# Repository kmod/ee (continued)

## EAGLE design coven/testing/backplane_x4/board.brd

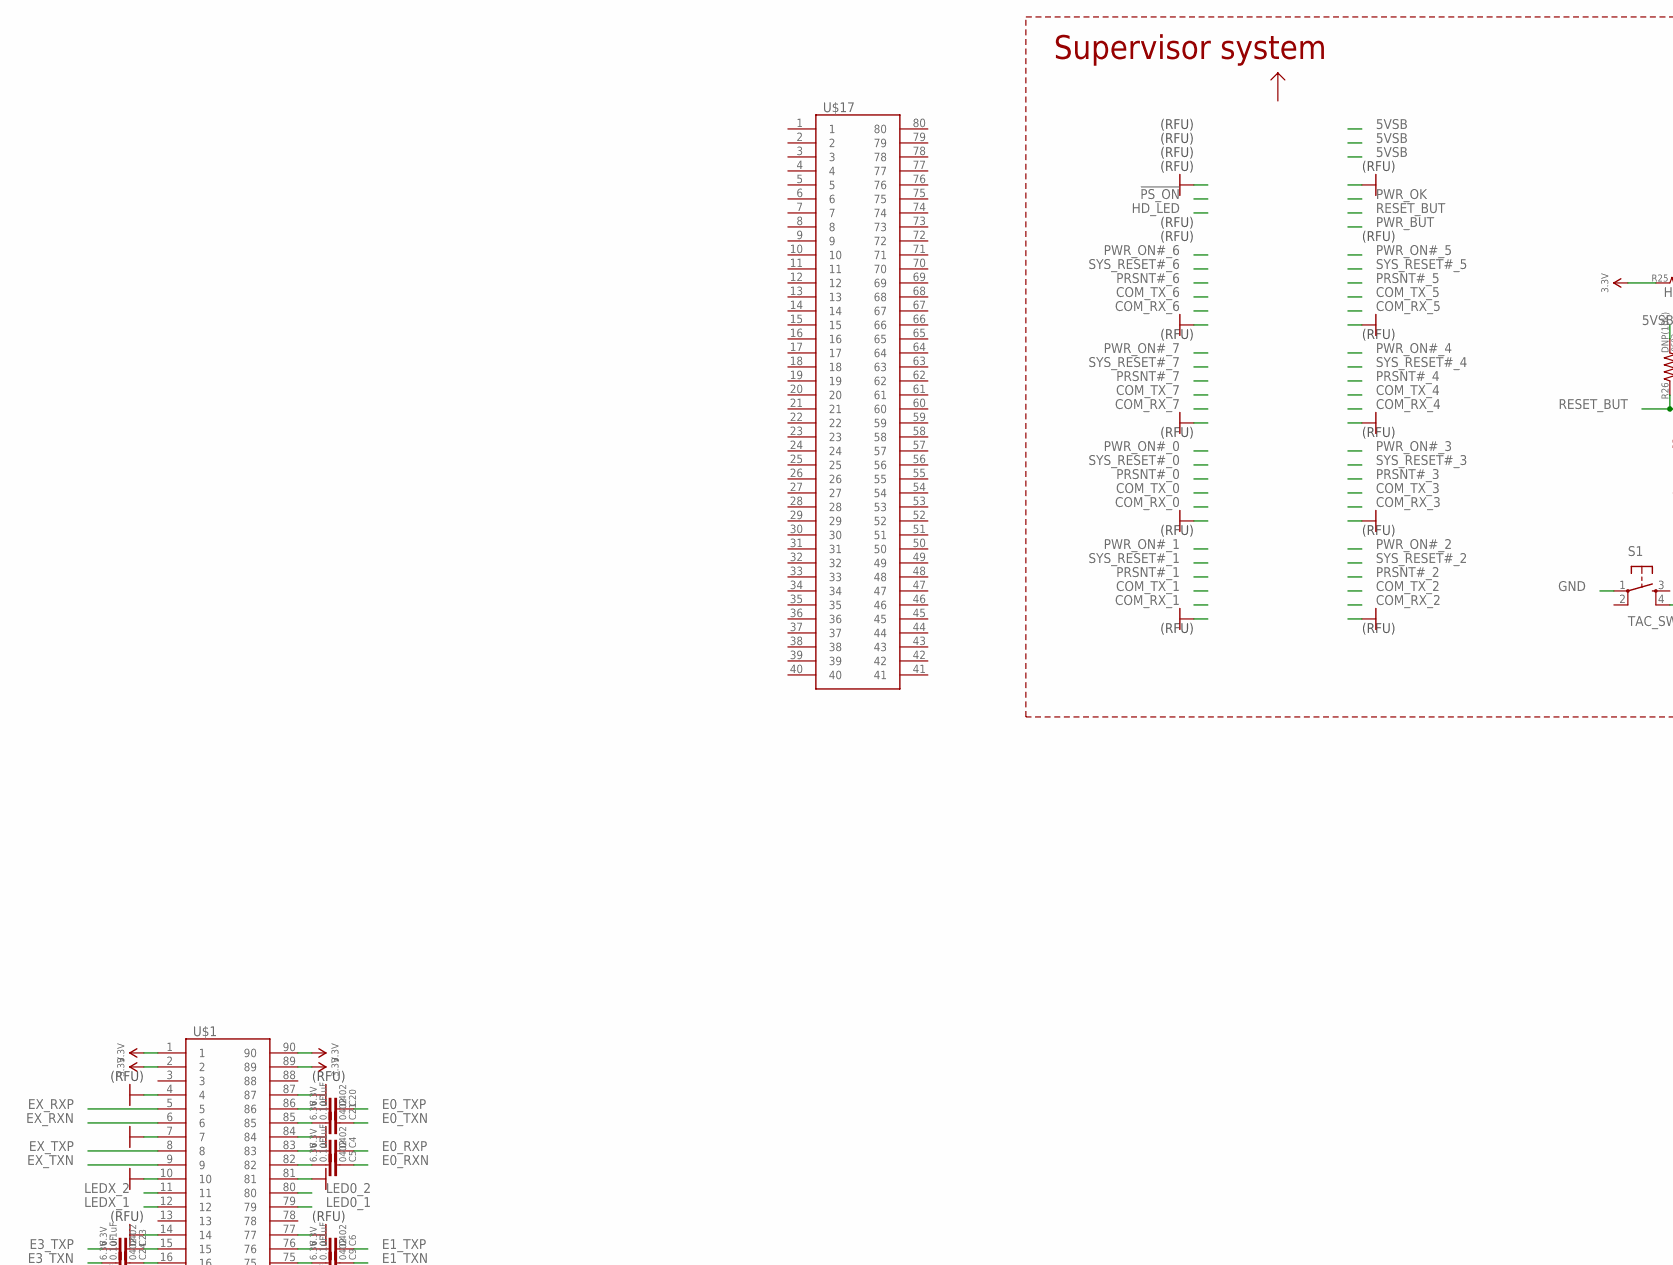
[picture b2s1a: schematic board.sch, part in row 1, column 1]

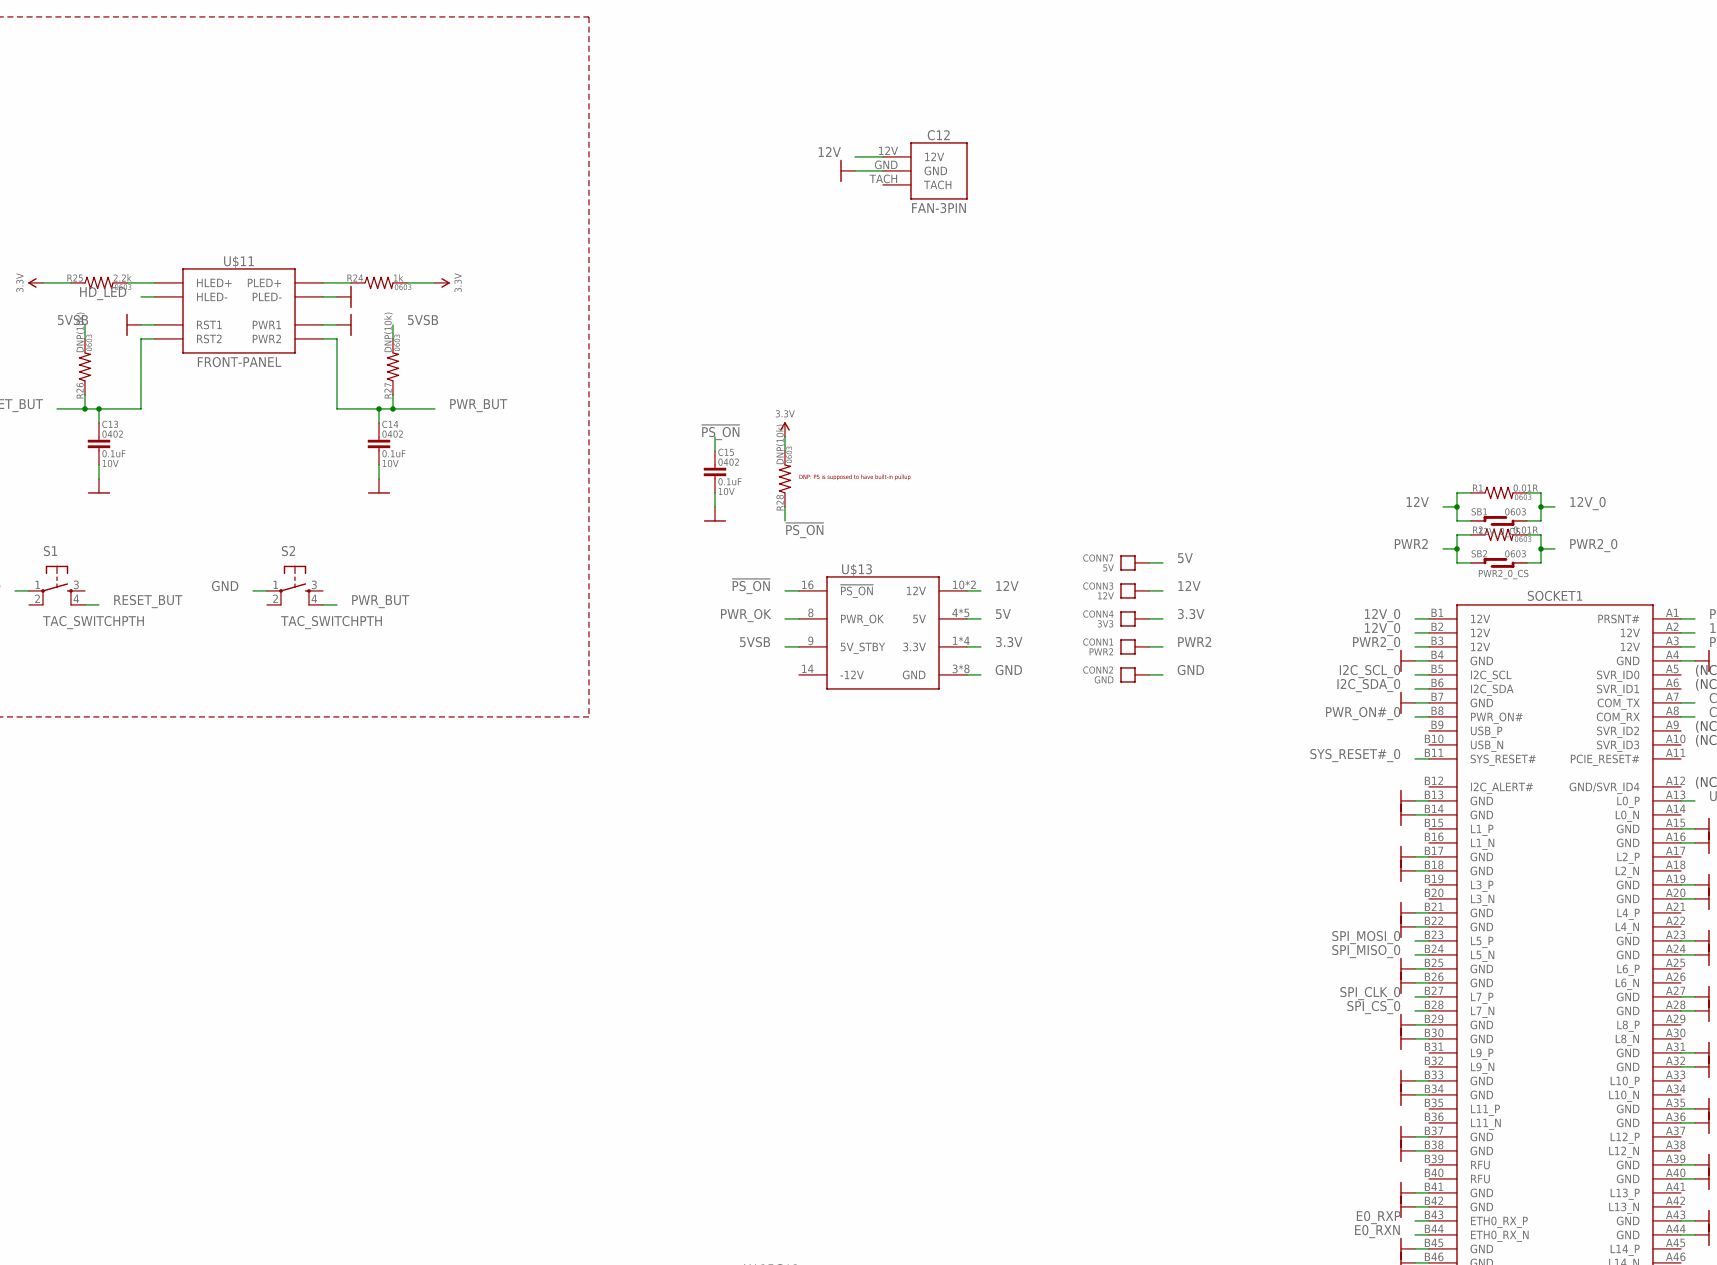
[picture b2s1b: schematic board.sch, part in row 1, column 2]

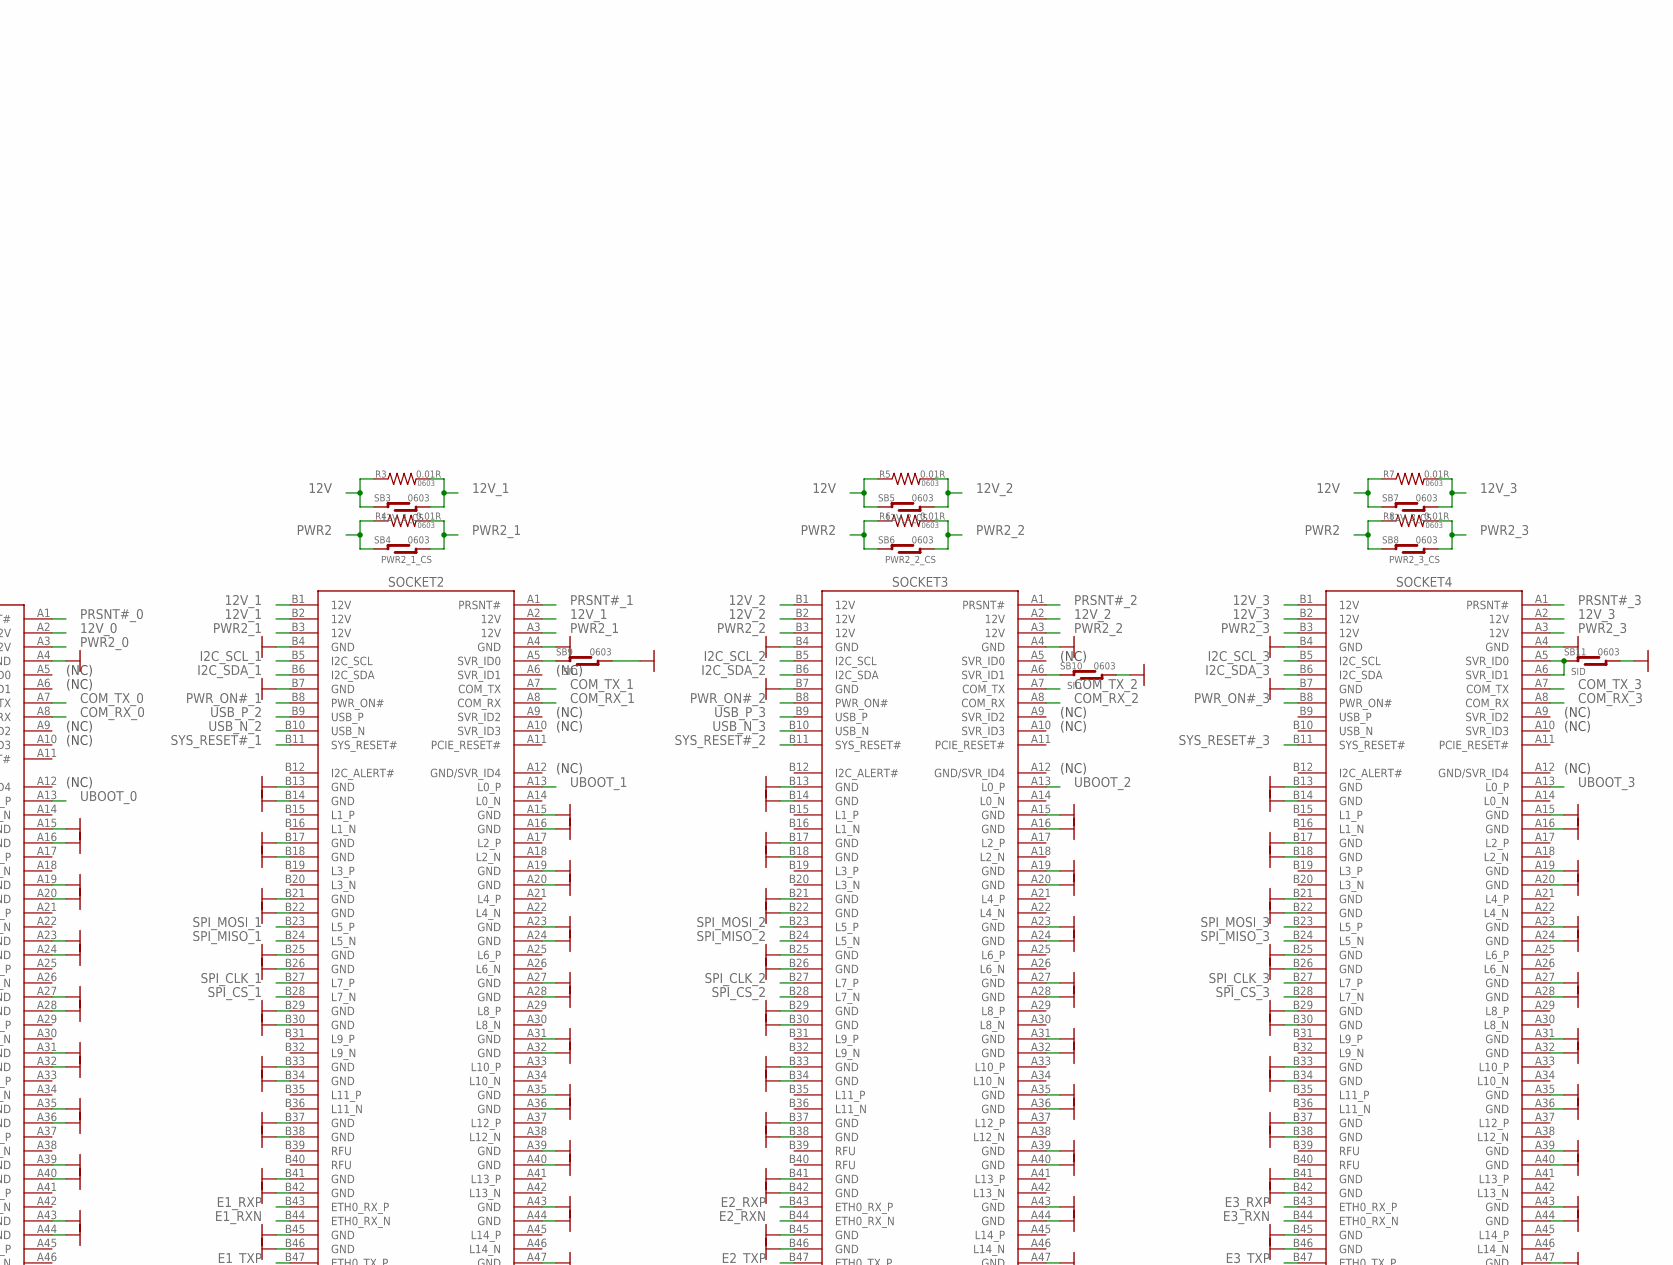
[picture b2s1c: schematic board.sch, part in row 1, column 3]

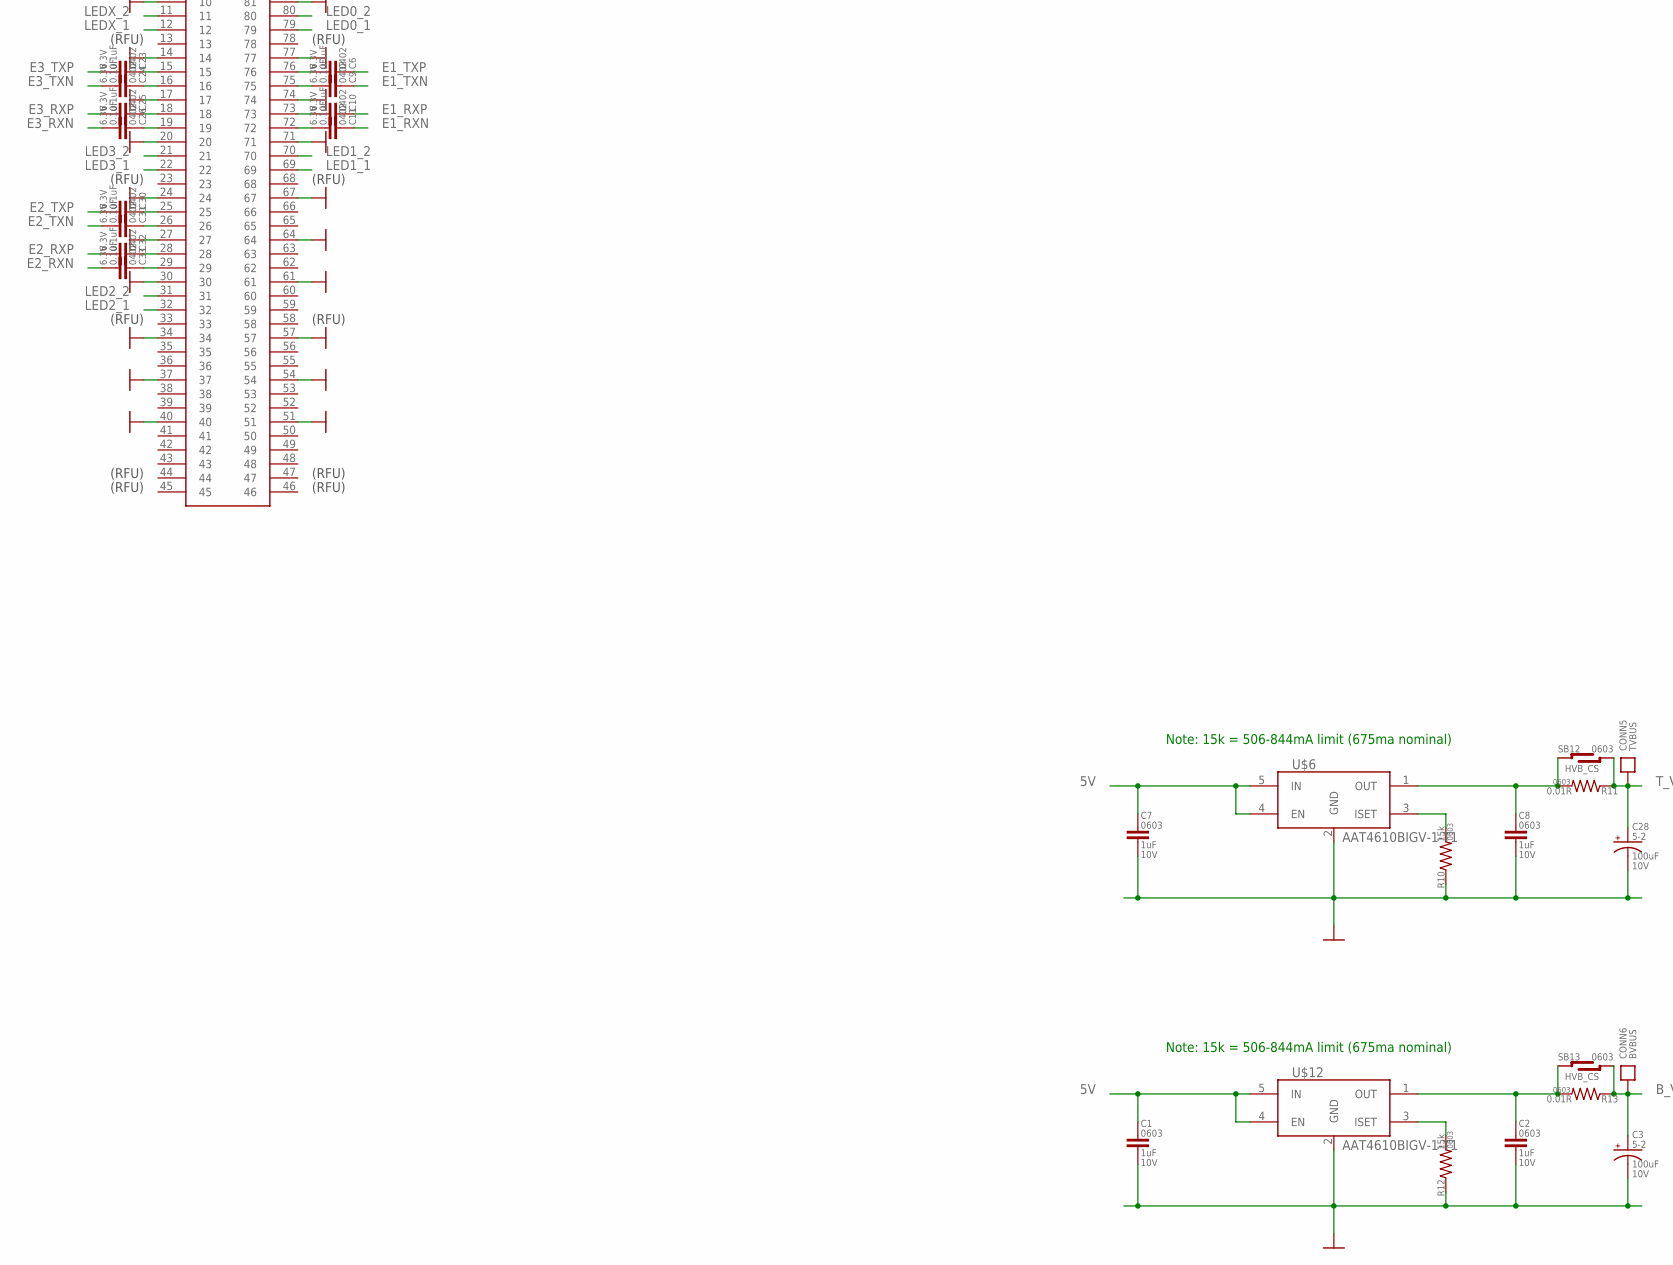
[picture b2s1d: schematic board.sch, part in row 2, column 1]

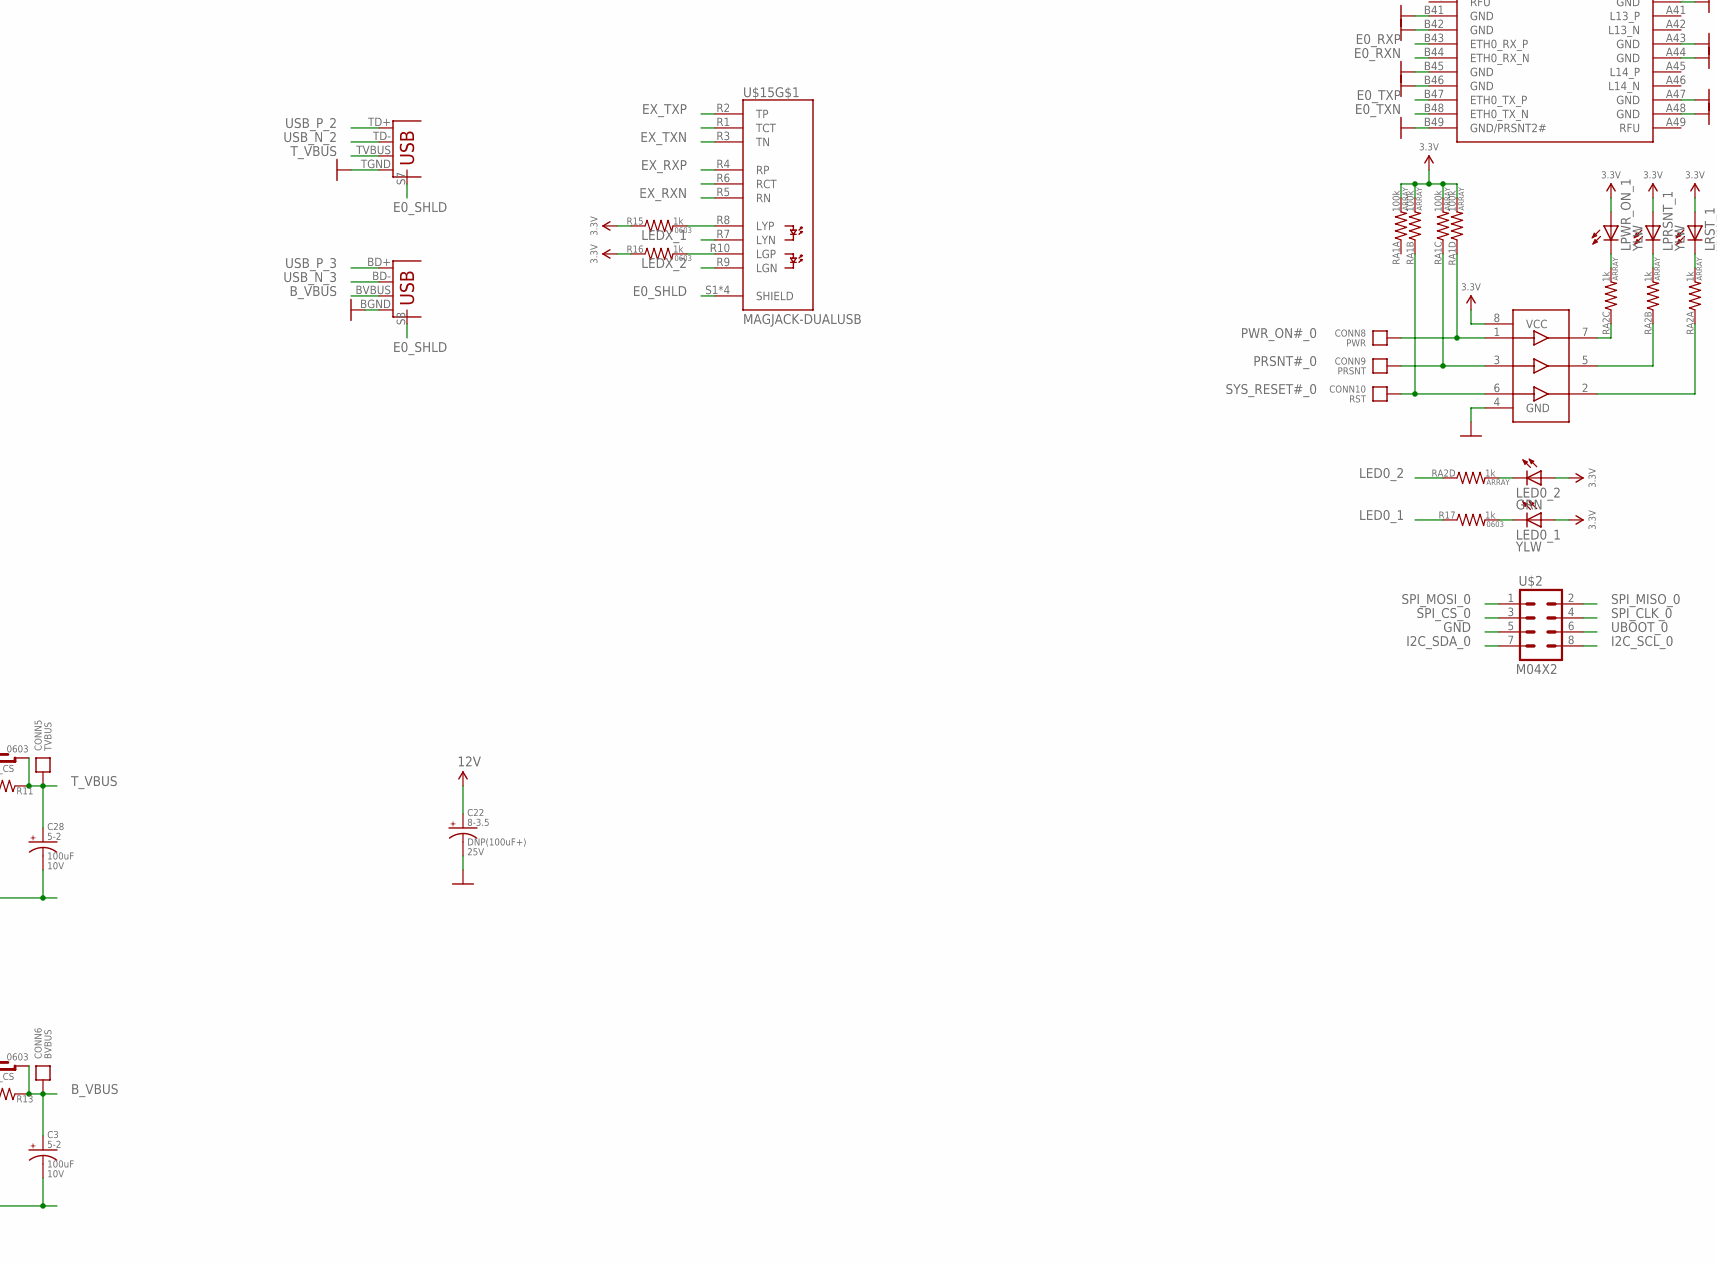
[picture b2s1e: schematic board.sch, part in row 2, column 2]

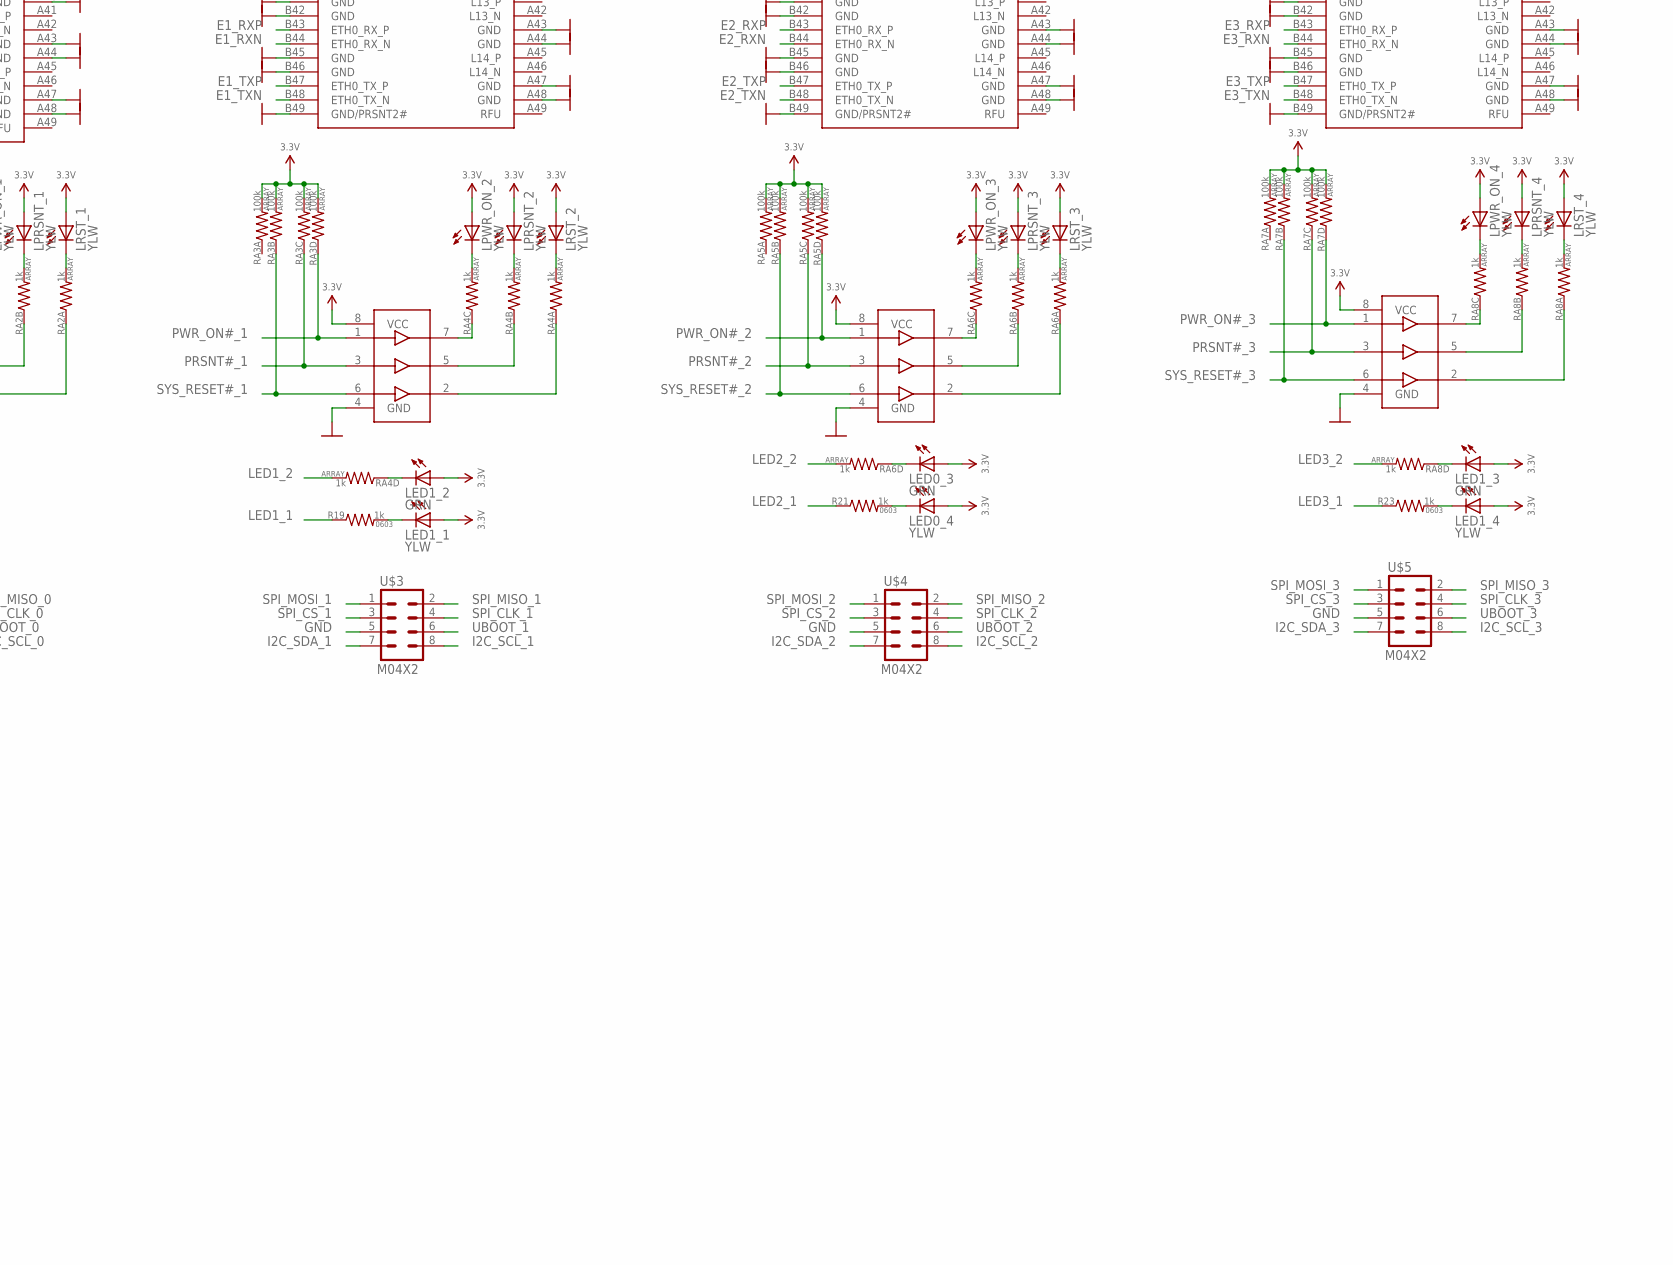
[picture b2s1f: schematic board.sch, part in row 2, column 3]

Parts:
C1, C2, C7, C8: 1uF; 0603-CAP; VOLTAGE 10V
C3, C28: 100uF; CAP-5-2; VOLTAGE 10V
C4, C5, C6, C9, C10, C11, C20, C21, C23, C24, C25, C26, C30, C31, C32, C33: 0.1uF; 0402-CAP
C12: FAN-3PIN
C13, C14, C15: 0.1uF; 0402-CAP; VOLTAGE 10V
C22: DNP(100uF+); CAP-8-3.5; VOLTAGE 25V
CONN1: PWR2; HOLE_18AWG
CONN2: GND; HOLE_18AWG
CONN3: 12V; HOLE_18AWG
CONN4: 3V3; HOLE_18AWG
CONN5: TVBUS; HOLE_22AWG
CONN6: BVBUS; HOLE_22AWG
CONN7: 5V; HOLE_18AWG
CONN8: PWR; TESTPAD-1.27
CONN9: PRSNT; TESTPAD-1.27
CONN10: RST; TESTPAD-1.27
IC1, IC2, IC3, IC4: 74X3G34; TSSOP8
LED0_1, LED0_4, LED1_1, LED1_4: YLW; 0603_LED
LED0_2, LED0_3, LED1_2, LED1_3: GRN; 0603_LED
LPRSNT_1, LPRSNT_2, LPRSNT_3, LPRSNT_4: YLW; 0603_LED
LPWR_ON_1, LPWR_ON_2, LPWR_ON_3, LPWR_ON_4: YLW; 0603_LED
LRST_1, LRST_2, LRST_3, LRST_4: YLW; 0603_LED
R1, R2, R3, R4, R5, R6, R7, R8, R11, R13: 0.01R; 0603-RES
R10, R12: 15k; 0603-RES
R15, R16, R17, R19, R21, R23, R24: 1k; 0603-RES
R25: 2.2k; 0603-RES
R26, R27, R28: DNP(10k); 0603-RES
RA1, RA3, RA5, RA7: 100k; 0603-ARV
RA2, RA4, RA6, RA8: 1k; 0603-ARV
S1, S2: TAC_SWITCHPTH; TACTILE-PTH
SB1: 12V_0_CS; SB-0603
SB2: PWR2_0_CS; SB-0603
SB3: 12V_1_CS; SB-0603
SB4: PWR2_1_CS; SB-0603
SB5: 12V_2_CS; SB-0603
SB6: PWR2_2_CS; SB-0603
SB7: 12V_3_CS; SB-0603
SB8: PWR2_3_CS; SB-0603
SB9, SB10, SB11: SID; SB-0603
SB12, SB13: HVB_CS; SB-0603
SOCKET1, SOCKET2, SOCKET3, SOCKET4: COVEN-V1CONN; CVN-V1-CONN
U$1: DF40-90RCP; DF40-RCP-90
U$2, U$3, U$4, U$5: M04X2; 2X4
U$6, U$12: AAT4610BIGV-1-T1; SOT23-5
U$11: FRONT-PANEL
U$13: ATX-PWRVERT; ATX-24-VERT
U$15: MAGJACK-DUALUSB
U$17: DF40-80RCP; DF40-RCP-80

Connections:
3.3V: CONN4.P$1, IC1.8 (VCC), IC2.8 (VCC), IC3.8 (VCC), IC4.8 (VCC), LED0_1.A, LED0_2.A, LED0_3.A, LED0_4.A, LED1_1.A, LED1_2.A, LED1_3.A, LED1_4.A, LPRSNT_1.A, LPRSNT_2.A, LPRSNT_3.A, LPRSNT_4.A, LPWR_ON_1.A, LPWR_ON_2.A, LPWR_ON_3.A, LPWR_ON_4.A, LRST_1.A, LRST_2.A, LRST_3.A, LRST_4.A, R15.1, R16.1, R24.2, R25.1, R28.2, RA1.5 (2), RA1.6 (2), RA1.7 (2), RA1.8 (2), RA3.5 (2), RA3.6 (2), RA3.7 (2), RA3.8 (2), RA5.5 (2), RA5.6 (2), RA5.7 (2), RA5.8 (2), RA7.5 (2), RA7.6 (2), RA7.7 (2), RA7.8 (2), U$1.1, U$1.2, U$1.89, U$1.90, U$13.1 (3.3V), U$13.2 (3.3V), U$13.12 (3.3V), U$13.13 (3.3V)
5V: C1.1, C7.1, CONN7.P$1, U$6.4 (EN), U$6.5 (IN), U$12.4 (EN), U$12.5 (IN), U$13.4 (5V), U$13.6 (5V), U$13.21 (5V), U$13.22 (5V), U$13.23 (5V)
5VSB: R26.2, R27.2, U$13.9 (5V_STBY)
12V: C12.12V, C22.1 (+), CONN3.P$1, R1.1, R3.1, R5.1, R7.1, SB1.L1, SB1.L2, SB3.L1, SB3.L2, SB5.L1, SB5.L2, SB7.L1, SB7.L2, U$13.10 (12V), U$13.11 (12V)
12V_0: R1.2, SB1.R1, SB1.R2, SOCKET1.A2 (12V), SOCKET1.B1 (12V), SOCKET1.B2 (12V)
12V_1: R3.2, SB3.R1, SB3.R2, SOCKET2.A2 (12V), SOCKET2.B1 (12V), SOCKET2.B2 (12V)
12V_2: R5.2, SB5.R1, SB5.R2, SOCKET3.A2 (12V), SOCKET3.B1 (12V), SOCKET3.B2 (12V)
12V_3: R7.2, SB7.R1, SB7.R2, SOCKET4.A2 (12V), SOCKET4.B1 (12V), SOCKET4.B2 (12V)
!PS_ON: C15.1, R28.1, U$13.16 (!PS_ON)
B_VBUS: C3.1 (+), CONN6.P, R13.1, SB13.R1, SB13.R2, U$15.BVBUS (VBUS)
COM_RX_0: SOCKET1.A8 (COM_RX)
COM_RX_1: SOCKET2.A8 (COM_RX)
COM_RX_2: SOCKET3.A8 (COM_RX)
COM_RX_3: SOCKET4.A8 (COM_RX)
COM_TX_0: SOCKET1.A7 (COM_TX)
COM_TX_1: SOCKET2.A7 (COM_TX)
COM_TX_2: SOCKET3.A7 (COM_TX)
COM_TX_3: SOCKET4.A7 (COM_TX)
E0_RXN: C5.1, SOCKET1.B44 (ETH0_RX_N)
E0_RXP: C4.1, SOCKET1.B43 (ETH0_RX_P)
E0_SHLD: U$15.S1 (SHIELD), U$15.S2 (SHIELD), U$15.S3 (SHIELD), U$15.S4 (SHIELD), U$15.S7 (SHELL), U$15.S8 (SHELL)
E0_TXN: C21.1, SOCKET1.B48 (ETH0_TX_N)
E0_TXP: C20.1, SOCKET1.B47 (ETH0_TX_P)
E1_RXN: C11.1, SOCKET2.B44 (ETH0_RX_N)
E1_RXP: C10.1, SOCKET2.B43 (ETH0_RX_P)
E1_TXN: C9.1, SOCKET2.B48 (ETH0_TX_N)
E1_TXP: C6.1, SOCKET2.B47 (ETH0_TX_P)
E2_RXN: C33.2, SOCKET3.B44 (ETH0_RX_N)
E2_RXP: C32.2, SOCKET3.B43 (ETH0_RX_P)
E2_TXN: C31.2, SOCKET3.B48 (ETH0_TX_N)
E2_TXP: C30.2, SOCKET3.B47 (ETH0_TX_P)
E3_RXN: C26.2, SOCKET4.B44 (ETH0_RX_N)
E3_RXP: C25.2, SOCKET4.B43 (ETH0_RX_P)
E3_TXN: C24.2, SOCKET4.B48 (ETH0_TX_N)
E3_TXP: C23.2, SOCKET4.B47 (ETH0_TX_P)
EX_RXN: U$1.6, U$15.R5 (RN)
EX_RXP: U$1.5, U$15.R4 (RP)
EX_TXN: U$1.9, U$15.R3 (TN)
EX_TXP: U$1.8, U$15.R2 (TP)
GND: C1.2, C2.2, C3.2 (-), C7.2, C8.2, C12.GND, C13.2, C14.2, C15.2, C22.2 (-), C28.2 (-), CONN2.P$1, IC1.4 (GND), IC2.4 (GND), IC3.4 (GND), IC4.4 (GND), R10.1, R12.1, S1.1, S2.1, SB9.R1, SB9.R2, SB10.R1, SB10.R2, SB11.R1, SB11.R2, SOCKET1.A4 (GND), SOCKET1.A15 (GND), SOCKET1.A16 (GND), SOCKET1.A19 (GND), SOCKET1.A20 (GND), SOCKET1.A23 (GND), SOCKET1.A24 (GND), SOCKET1.A27 (GND), SOCKET1.A28 (GND), SOCKET1.A31 (GND), SOCKET1.A32 (GND), SOCKET1.A35 (GND), SOCKET1.A36 (GND), SOCKET1.A39 (GND), SOCKET1.A40 (GND), SOCKET1.A43 (GND), SOCKET1.A44 (GND), SOCKET1.A47 (GND), SOCKET1.A48 (GND), SOCKET1.B4 (GND), SOCKET1.B7 (GND), SOCKET1.B13 (GND), SOCKET1.B14 (GND), SOCKET1.B17 (GND), SOCKET1.B18 (GND), SOCKET1.B21 (GND), SOCKET1.B22 (GND), SOCKET1.B25 (GND), SOCKET1.B26 (GND), SOCKET1.B29 (GND), SOCKET1.B30 (GND), SOCKET1.B33 (GND), SOCKET1.B34 (GND), SOCKET1.B37 (GND), SOCKET1.B38 (GND), SOCKET1.B41 (GND), SOCKET1.B42 (GND), SOCKET1.B45 (GND), SOCKET1.B46 (GND), SOCKET1.B49 (GND/PRSNT2#), SOCKET2.A4 (GND), SOCKET2.A15 (GND), SOCKET2.A16 (GND), SOCKET2.A19 (GND), SOCKET2.A20 (GND), SOCKET2.A23 (GND), SOCKET2.A24 (GND), SOCKET2.A27 (GND), SOCKET2.A28 (GND), SOCKET2.A31 (GND), SOCKET2.A32 (GND), SOCKET2.A35 (GND), SOCKET2.A36 (GND), SOCKET2.A39 (GND), SOCKET2.A40 (GND), SOCKET2.A43 (GND), SOCKET2.A44 (GND), SOCKET2.A47 (GND), SOCKET2.A48 (GND), SOCKET2.B4 (GND), SOCKET2.B7 (GND), SOCKET2.B13 (GND), SOCKET2.B14 (GND), SOCKET2.B17 (GND), SOCKET2.B18 (GND), SOCKET2.B21 (GND), SOCKET2.B22 (GND), SOCKET2.B25 (GND), SOCKET2.B26 (GND), SOCKET2.B29 (GND), SOCKET2.B30 (GND), SOCKET2.B33 (GND), SOCKET2.B34 (GND), SOCKET2.B37 (GND), SOCKET2.B38 (GND), SOCKET2.B41 (GND), SOCKET2.B42 (GND), SOCKET2.B45 (GND), SOCKET2.B46 (GND), SOCKET2.B49 (GND/PRSNT2#), SOCKET3.A4 (GND), SOCKET3.A15 (GND), SOCKET3.A16 (GND), SOCKET3.A19 (GND), SOCKET3.A20 (GND), SOCKET3.A23 (GND), SOCKET3.A24 (GND), SOCKET3.A27 (GND), SOCKET3.A28 (GND), SOCKET3.A31 (GND), SOCKET3.A32 (GND), SOCKET3.A35 (GND), SOCKET3.A36 (GND), SOCKET3.A39 (GND), SOCKET3.A40 (GND), SOCKET3.A43 (GND), SOCKET3.A44 (GND), SOCKET3.A47 (GND), SOCKET3.A48 (GND), SOCKET3.B4 (GND), SOCKET3.B7 (GND), SOCKET3.B13 (GND), SOCKET3.B14 (GND), SOCKET3.B17 (GND), SOCKET3.B18 (GND), SOCKET3.B21 (GND), SOCKET3.B22 (GND), SOCKET3.B25 (GND), SOCKET3.B26 (GND), SOCKET3.B29 (GND), SOCKET3.B30 (GND), SOCKET3.B33 (GND), SOCKET3.B34 (GND), SOCKET3.B37 (GND), SOCKET3.B38 (GND), SOCKET3.B41 (GND), SOCKET3.B42 (GND), SOCKET3.B45 (GND), SOCKET3.B46 (GND), SOCKET3.B49 (GND/PRSNT2#), SOCKET4.A4 (GND), SOCKET4.A15 (GND), SOCKET4.A16 (GND), SOCKET4.A19 (GND), SOCKET4.A20 (GND), SOCKET4.A23 (GND), SOCKET4.A24 (GND), SOCKET4.A27 (GND), SOCKET4.A28 (GND), SOCKET4.A31 (GND), SOCKET4.A32 (GND), SOCKET4.A35 (GND), SOCKET4.A36 (GND), SOCKET4.A39 (GND), SOCKET4.A40 (GND), SOCKET4.A43 (GND), SOCKET4.A44 (GND), SOCKET4.A47 (GND), SOCKET4.A48 (GND), SOCKET4.B4 (GND), SOCKET4.B7 (GND), SOCKET4.B13 (GND), SOCKET4.B14 (GND), SOCKET4.B17 (GND), SOCKET4.B18 (GND), SOCKET4.B21 (GND), SOCKET4.B22 (GND), SOCKET4.B25 (GND), SOCKET4.B26 (GND), SOCKET4.B29 (GND), SOCKET4.B30 (GND), SOCKET4.B33 (GND), SOCKET4.B34 (GND), SOCKET4.B37 (GND), SOCKET4.B38 (GND), SOCKET4.B41 (GND), SOCKET4.B42 (GND), SOCKET4.B45 (GND), SOCKET4.B46 (GND), SOCKET4.B49 (GND/PRSNT2#), U$1.4, U$1.7, U$1.10, U$1.14, U$1.17, U$1.20, U$1.24, U$1.27, U$1.30, U$1.34, U$1.37, U$1.40, U$1.51, U$1.54, U$1.57, U$1.61, U$1.64, U$1.67, U$1.71, U$1.74, U$1.77, U$1.81, U$1.84, U$1.87, U$2.5, U$3.5, U$4.5, U$5.5, U$6.2 (GND), U$11.PLED-, U$11.PWR_1 (PWR1), U$11.RST_1 (RST1), U$12.2 (GND), U$13.3 (GND), U$13.5 (GND), U$13.7 (GND), U$13.15 (GND), U$13.17 (GND), U$13.18 (GND), U$13.19 (GND), U$13.24 (GND), U$15.BGND (GND), U$15.TGND (GND)
HD_LED: U$11.HDLED- (HLED-)
HOST_VBUS_U: C8.1, R11.2, SB12.L1, SB12.L2, U$6.1 (OUT)
HOST_VBUS_U1: C2.1, R13.2, SB13.L1, SB13.L2, U$12.1 (OUT)
I2C_SCL_0: SOCKET1.B5 (I2C_SCL), U$2.8
I2C_SCL_1: SOCKET2.B5 (I2C_SCL), U$3.8
I2C_SCL_2: SOCKET3.B5 (I2C_SCL), U$4.8
I2C_SCL_3: SOCKET4.B5 (I2C_SCL), U$5.8
I2C_SDA_0: SOCKET1.B6 (I2C_SDA), U$2.7
I2C_SDA_1: SOCKET2.B6 (I2C_SDA), U$3.7
I2C_SDA_2: SOCKET3.B6 (I2C_SDA), U$4.7
I2C_SDA_3: SOCKET4.B6 (I2C_SDA), U$5.7
LED0_1: R17.1, U$1.79
LED0_2: RA2.4 (1), U$1.80
LED1_1: R19.1, U$1.69
LED1_2: RA4.5 (2), U$1.70
LED2_1: R21.1, U$1.32
LED2_2: RA6.5 (2), U$1.31
LED3_1: R23.1, U$1.22
LED3_2: RA8.5 (2), U$1.21
LEDX_1: U$1.12, U$15.R7 (LYN)
LEDX_2: U$1.11, U$15.R9 (LGN)
unnamed: SB9.L1, SB9.L2, SOCKET2.A5 (SVR_ID0)
unnamed: SB11.L1, SB11.L2, SOCKET4.A5 (SVR_ID0), SOCKET4.A6 (SVR_ID1)
unnamed: SB10.L1, SB10.L2, SOCKET3.A6 (SVR_ID1)
unnamed: IC2.7 (1Y), RA4.3 (1)
unnamed: IC2.5 (2Y), RA4.2 (1)
unnamed: LPWR_ON_2.C, RA4.6 (2)
unnamed: LPWR_ON_1.C, RA2.6 (2)
unnamed: LPRSNT_1.C, RA2.7 (2)
unnamed: IC1.7 (1Y), RA2.3 (1)
unnamed: IC1.5 (2Y), RA2.2 (1)
unnamed: IC1.2 (3Y), RA2.1
unnamed: LRST_1.C, RA2.8 (2)
unnamed: LPRSNT_2.C, RA4.7 (2)
unnamed: IC2.2 (3Y), RA4.1
unnamed: LRST_2.C, RA4.8 (2)
unnamed: IC3.7 (1Y), RA6.3 (1)
unnamed: IC3.5 (2Y), RA6.2 (1)
unnamed: LPWR_ON_3.C, RA6.6 (2)
unnamed: LPRSNT_3.C, RA6.7 (2)
unnamed: IC3.2 (3Y), RA6.1
unnamed: LRST_3.C, RA6.8 (2)
unnamed: IC4.7 (1Y), RA8.3 (1)
unnamed: IC4.5 (2Y), RA8.2 (1)
unnamed: LPWR_ON_4.C, RA8.6 (2)
unnamed: LPRSNT_4.C, RA8.7 (2)
unnamed: IC4.2 (3Y), RA8.1
unnamed: LRST_4.C, RA8.8 (2)
unnamed: C11.2, U$1.72
unnamed: C10.2, U$1.73
unnamed: R10.2, U$6.3 (ISET)
unnamed: R12.2, U$12.3 (ISET)
unnamed: R25.2, U$11.HDLED+ (HLED+)
unnamed: R15.2, U$15.R8 (LYP)
unnamed: C9.2, U$1.75
unnamed: R16.2, U$15.R10 (LGP)
unnamed: C6.2, U$1.76
unnamed: R24.1, U$11.PLED+
unnamed: C5.2, U$1.82
unnamed: C4.2, U$1.83
unnamed: C21.2, U$1.85
unnamed: C20.2, U$1.86
unnamed: C33.1, U$1.29
unnamed: C32.1, U$1.28
unnamed: C31.1, U$1.26
unnamed: C30.1, U$1.25
unnamed: C25.1, U$1.18
unnamed: C24.1, U$1.16
unnamed: C23.1, U$1.15
unnamed: LED0_1.C, R17.2
unnamed: LED0_2.C, RA2.5 (2)
unnamed: LED1_2.C, RA4.4 (1)
unnamed: LED1_1.C, R19.2
unnamed: LED0_3.C, RA6.4 (1)
unnamed: LED0_4.C, R21.2
unnamed: LED1_3.C, RA8.4 (1)
unnamed: LED1_4.C, R23.2
unnamed: C26.1, U$1.19
PRSNT#_0: CONN9.P, IC1.3 (2A), RA1.3 (1), SOCKET1.A1 (PRSNT#)
PRSNT#_1: IC2.3 (2A), RA3.3 (1), SOCKET2.A1 (PRSNT#)
PRSNT#_2: IC3.3 (2A), RA5.3 (1), SOCKET3.A1 (PRSNT#)
PRSNT#_3: IC4.3 (2A), RA7.3 (1), SOCKET4.A1 (PRSNT#)
PWR2: CONN1.P$1, R2.1, R4.1, R6.1, R8.1, SB2.L1, SB2.L2, SB4.L1, SB4.L2, SB6.L1, SB6.L2, SB8.L1, SB8.L2
PWR2_0: R2.2, SB2.R1, SB2.R2, SOCKET1.A3 (12V), SOCKET1.B3 (12V)
PWR2_1: R4.2, SB4.R1, SB4.R2, SOCKET2.A3 (12V), SOCKET2.B3 (12V)
PWR2_2: R6.2, SB6.R1, SB6.R2, SOCKET3.A3 (12V), SOCKET3.B3 (12V)
PWR2_3: R8.2, SB8.R1, SB8.R2, SOCKET4.A3 (12V), SOCKET4.B3 (12V)
PWR_BUT: C14.1, R27.1, S2.4, U$11.PWR_2 (PWR2)
PWR_OK: U$13.8 (PWR_OK)
PWR_ON#_0: CONN8.P, IC1.1 (1A), RA1.4 (1), SOCKET1.B8 (PWR_ON#)
PWR_ON#_1: IC2.1 (1A), RA3.4 (1), SOCKET2.B8 (PWR_ON#)
PWR_ON#_2: IC3.1 (1A), RA5.4 (1), SOCKET3.B8 (PWR_ON#)
PWR_ON#_3: IC4.1 (1A), RA7.4 (1), SOCKET4.B8 (PWR_ON#)
RESET_BUT: C13.1, R26.1, S1.4, U$11.RST_2 (RST2)
SPI_CLK_0: SOCKET1.B27 (L7_P), U$2.4
SPI_CLK_1: SOCKET2.B27 (L7_P), U$3.4
SPI_CLK_2: SOCKET3.B27 (L7_P), U$4.4
SPI_CLK_3: SOCKET4.B27 (L7_P), U$5.4
SPI_CS_0: SOCKET1.B28 (L7_N), U$2.3
SPI_CS_1: SOCKET2.B28 (L7_N), U$3.3
SPI_CS_2: SOCKET3.B28 (L7_N), U$4.3
SPI_CS_3: SOCKET4.B28 (L7_N), U$5.3
SPI_MISO_0: SOCKET1.B24 (L5_N), U$2.2
SPI_MISO_1: SOCKET2.B24 (L5_N), U$3.2
SPI_MISO_2: SOCKET3.B24 (L5_N), U$4.2
SPI_MISO_3: SOCKET4.B24 (L5_N), U$5.2
SPI_MOSI_0: SOCKET1.B23 (L5_P), U$2.1
SPI_MOSI_1: SOCKET2.B23 (L5_P), U$3.1
SPI_MOSI_2: SOCKET3.B23 (L5_P), U$4.1
SPI_MOSI_3: SOCKET4.B23 (L5_P), U$5.1
SYS_RESET#_0: CONN10.P, IC1.6 (3A), RA1.2 (1), SOCKET1.B11 (SYS_RESET#)
SYS_RESET#_1: IC2.6 (3A), RA3.2 (1), SOCKET2.B11 (SYS_RESET#)
SYS_RESET#_2: IC3.6 (3A), RA5.2 (1), SOCKET3.B11 (SYS_RESET#)
SYS_RESET#_3: IC4.6 (3A), RA7.2 (1), SOCKET4.B11 (SYS_RESET#)
T_VBUS: C28.1 (+), CONN5.P, R11.1, SB12.R1, SB12.R2, U$15.TVBUS (VBUS)
UBOOT_0: SOCKET1.A13 (L0_P), U$2.6
UBOOT_1: SOCKET2.A13 (L0_P), U$3.6
UBOOT_2: SOCKET3.A13 (L0_P), U$4.6
UBOOT_3: SOCKET4.A13 (L0_P), U$5.6
USB_N_2: SOCKET2.B10 (USB_N), U$15.TD- (D-)
USB_N_3: SOCKET3.B10 (USB_N), U$15.BD- (D-)
USB_P_2: SOCKET2.B9 (USB_P), U$15.TD+ (D+)
USB_P_3: SOCKET3.B9 (USB_P), U$15.BD+ (D+)

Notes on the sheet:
(NC)
Note: 15k = 506-844mA limit (675ma nominal)
(RFU)
DNP: PS is supposed to have built-in pullup
Supervisor system

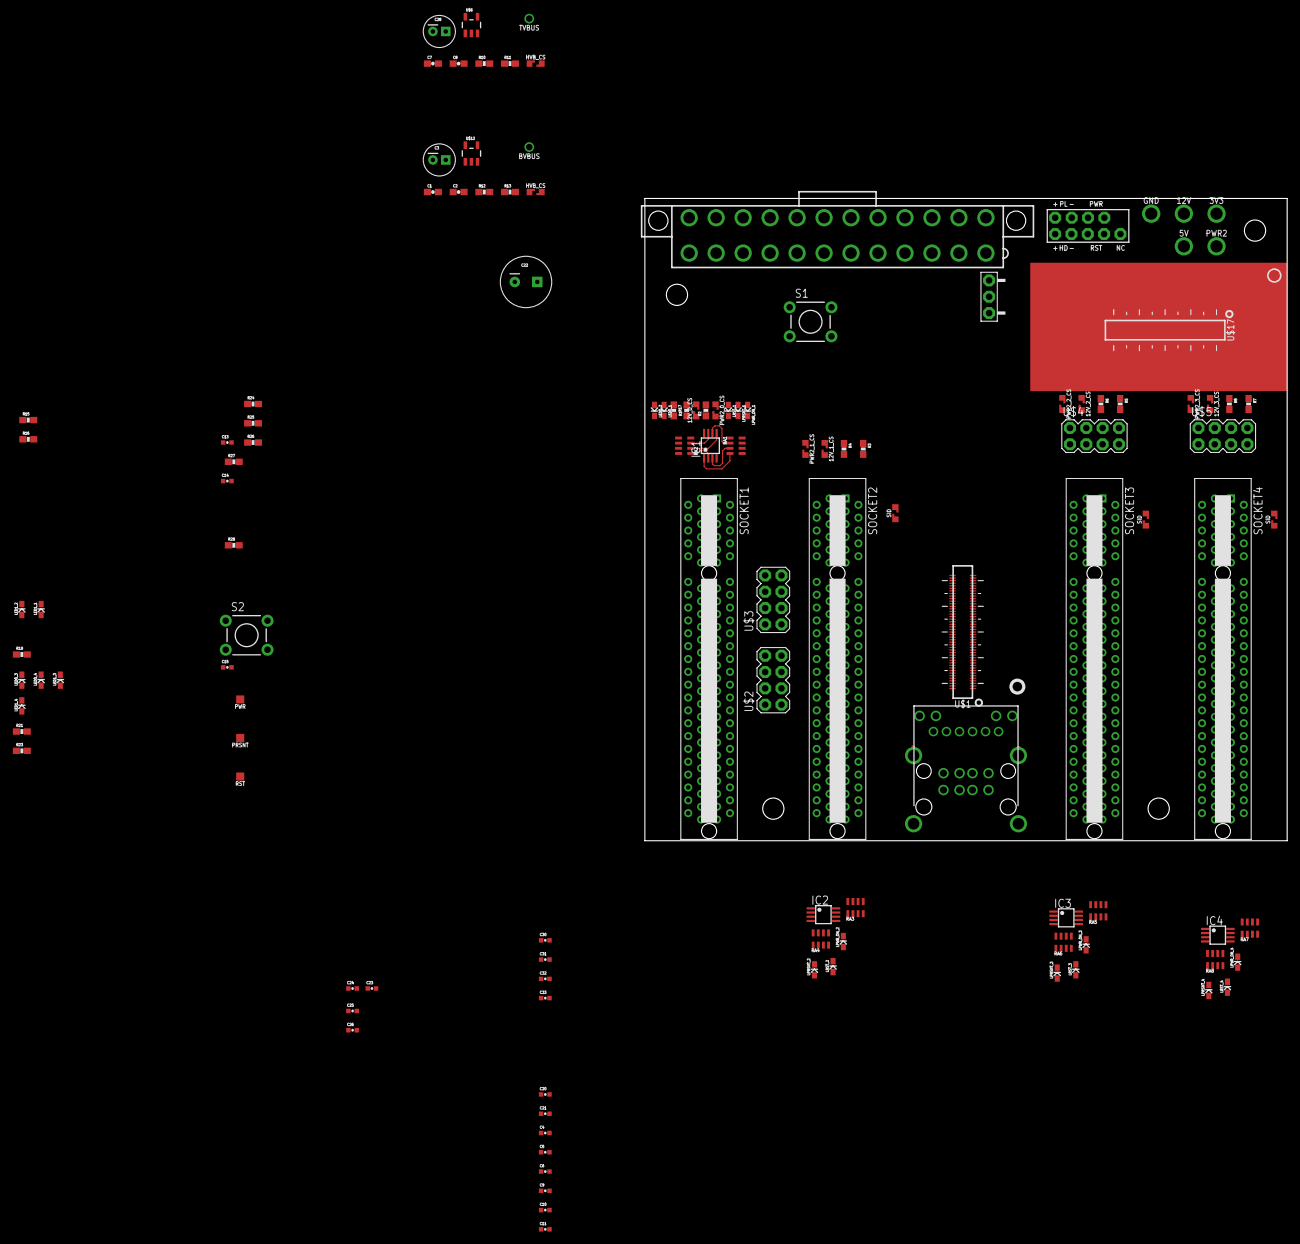
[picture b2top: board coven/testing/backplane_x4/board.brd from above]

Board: 4 copper layers, 100.0 x 100.0 mm, 126 parts (0 on the bottom side), 153 nets.

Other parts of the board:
U$7, U$8, U$9, U$10: STAND-OFF
